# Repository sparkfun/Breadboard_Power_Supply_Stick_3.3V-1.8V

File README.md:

SparkFun Breadboard Power Supply Stick - 3.3V/1.8V
=====================================

[*SparkFun Breadboard Power Supply Stick - 3.3V/1.8V (PRT-10934)*](https://www.sparkfun.com/products/13157)

This is a simple board that takes a 4-9V input voltage and outputs a selectable 1.8V or 3.3V regulated voltage.
All headers are 0.1" pitch for simple insertion into a breadboard. 

Repository Contents
-------------------
* **/Hardware** - All Eagle design files (.brd, .sch, .STL)
* **/Production** - Test bed files and production panel files

Product Versions
----------------
* [PRT-13157](https://www.sparkfun.com/products/13157)- Version 1.4. Currently available
* [PRT-10934](https://www.sparkfun.com/products/10934)- Version 1.0. Retired. 

Version History
---------------
* [v_14](https://github.com/sparkfun/Breadboard_Power_Supply_Stick_3.3V-1.8V/tree/v_14) GitHub files - version 1.4.  
* [v_10](https://github.com/sparkfun/Breadboard_Power_Supply_Stick_3.3V-1.8V/tree/v_10) GitHub files - version 1.0

License Information
-------------------
The hardware is released under [Creative Commons ShareAlike 4.0 International](https://creativecommons.org/licenses/by-sa/4.0/).

Distributed as-is; no warranty is given.

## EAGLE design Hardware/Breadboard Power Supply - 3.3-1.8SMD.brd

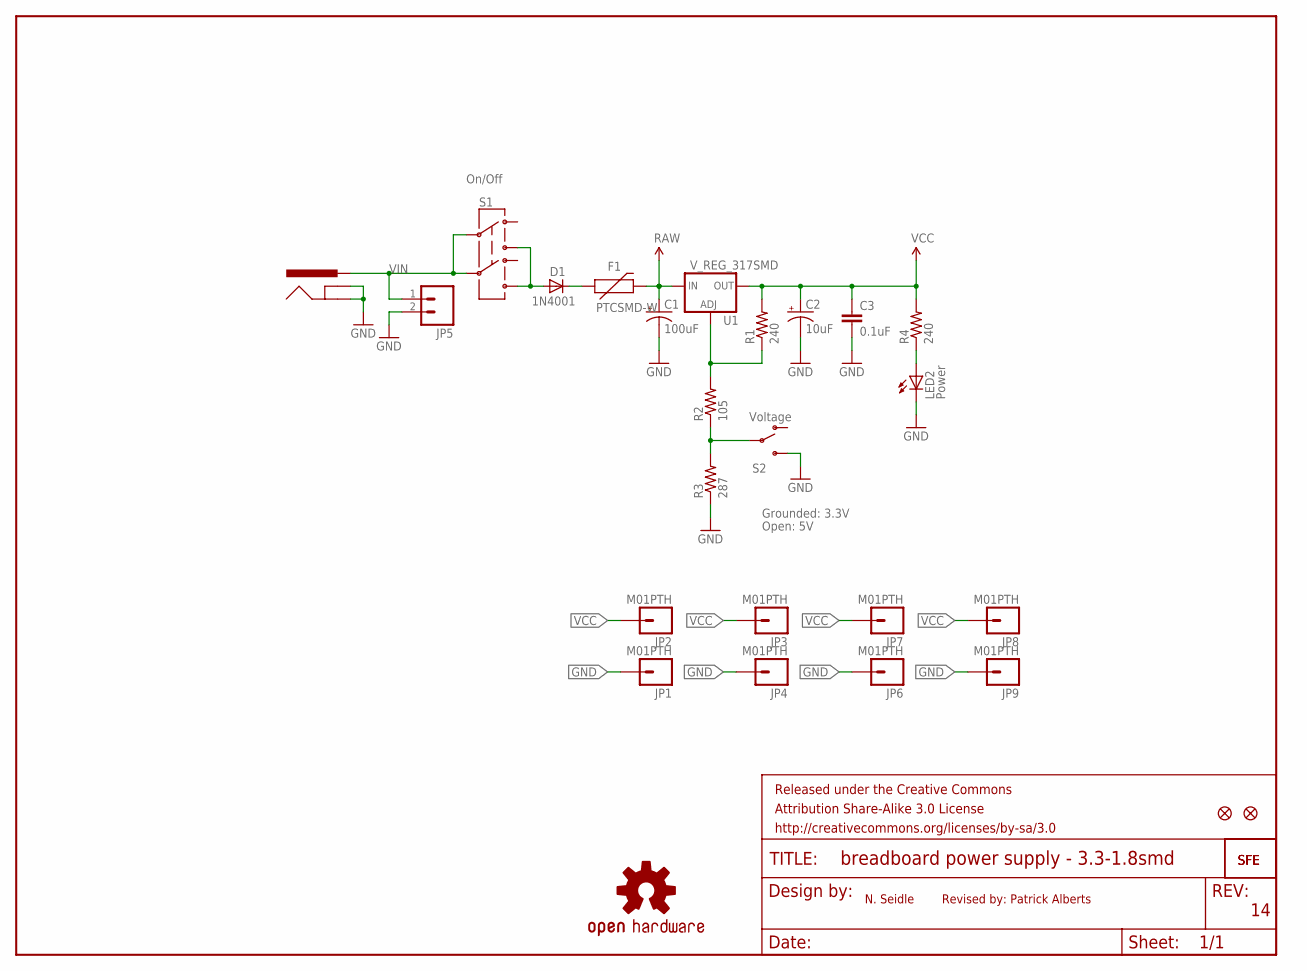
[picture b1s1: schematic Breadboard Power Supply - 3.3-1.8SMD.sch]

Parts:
C1: 100uF; EIA7343
C2: 10uF; EIA3216
C3: 0.1uF; 0603-CAP
D1: 1N4001; SMA-DIODE-TYLERALT1
F1: PTCSMD-W; PTC-1206-WIDE
FRAME1: FRAME-LETTER; CREATIVE_COMMONS
J1: POWER_JACKOVERPASTE_REDBOARD_0603; POWER_JACK_SMD_OVERPASTE_REDBOARD_0603
JP1, JP2, JP3, JP4, JP6, JP7, JP8, JP9: M01PTH; 1X01
JP5: M02PTH; 1X02
LED2: Power; LED-1206
LOGO1: OSHW-LOGOS; OSHW-LOGO-S
R1, R4: 240; 0603-RES
R2: 105; 0603-RES
R3: 287; 0603-RES
S1: On/Off; AYZ0202
S2: Voltage; AYZ0202
U1: V_REG_317SMD; SOT223
U$1: LOGO-SFESK; SFE-LOGO-FLAME
U$2: LOGO-SFENEW; SFE-NEW-WEBLOGO
U$3, U$4: FIDUCIAL1X2; FIDUCIAL-1X2

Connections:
GND: C1.C (-), C2.C (-), C3.2, J1.GND (GNDBREAK), J1.P$4 (GND), JP1.1, JP4.1, JP5.2, JP6.1, JP9.1, LED2.C, R3.1, S2.3 (S)
unnamed: D1.C, F1.1
unnamed: D1.A, S1.1 (3), S1.4 (6)
unnamed: R2.1, R3.2, S2.2
unnamed: R1.1, R2.2, U1.1 (ADJ)
unnamed: LED2.A, R4.1
RAW: C1.A (+), F1.2, U1.3 (IN)
VCC: C2.A (+), C3.1, JP2.1, JP3.1, JP7.1, JP8.1, R1.2, R4.2, U1.2 (OUT)
VIN: J1.VIN0 (PWR), JP5.1, S1.2, S1.5

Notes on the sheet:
Grounded: 3.3V
Open: 5V
N. Seidle
Revised by: Patrick Alberts

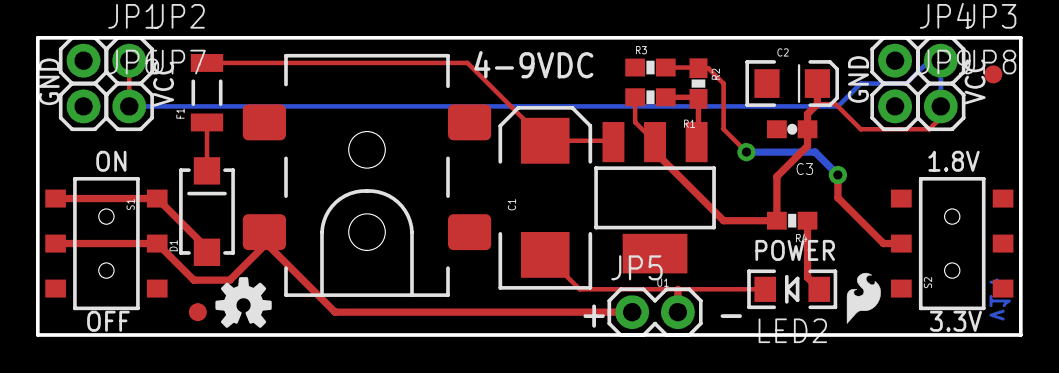
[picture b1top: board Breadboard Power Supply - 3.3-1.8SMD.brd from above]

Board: 2 copper layers, 54.6 x 16.5 mm, 29 parts (1 on the bottom side), 9 nets.

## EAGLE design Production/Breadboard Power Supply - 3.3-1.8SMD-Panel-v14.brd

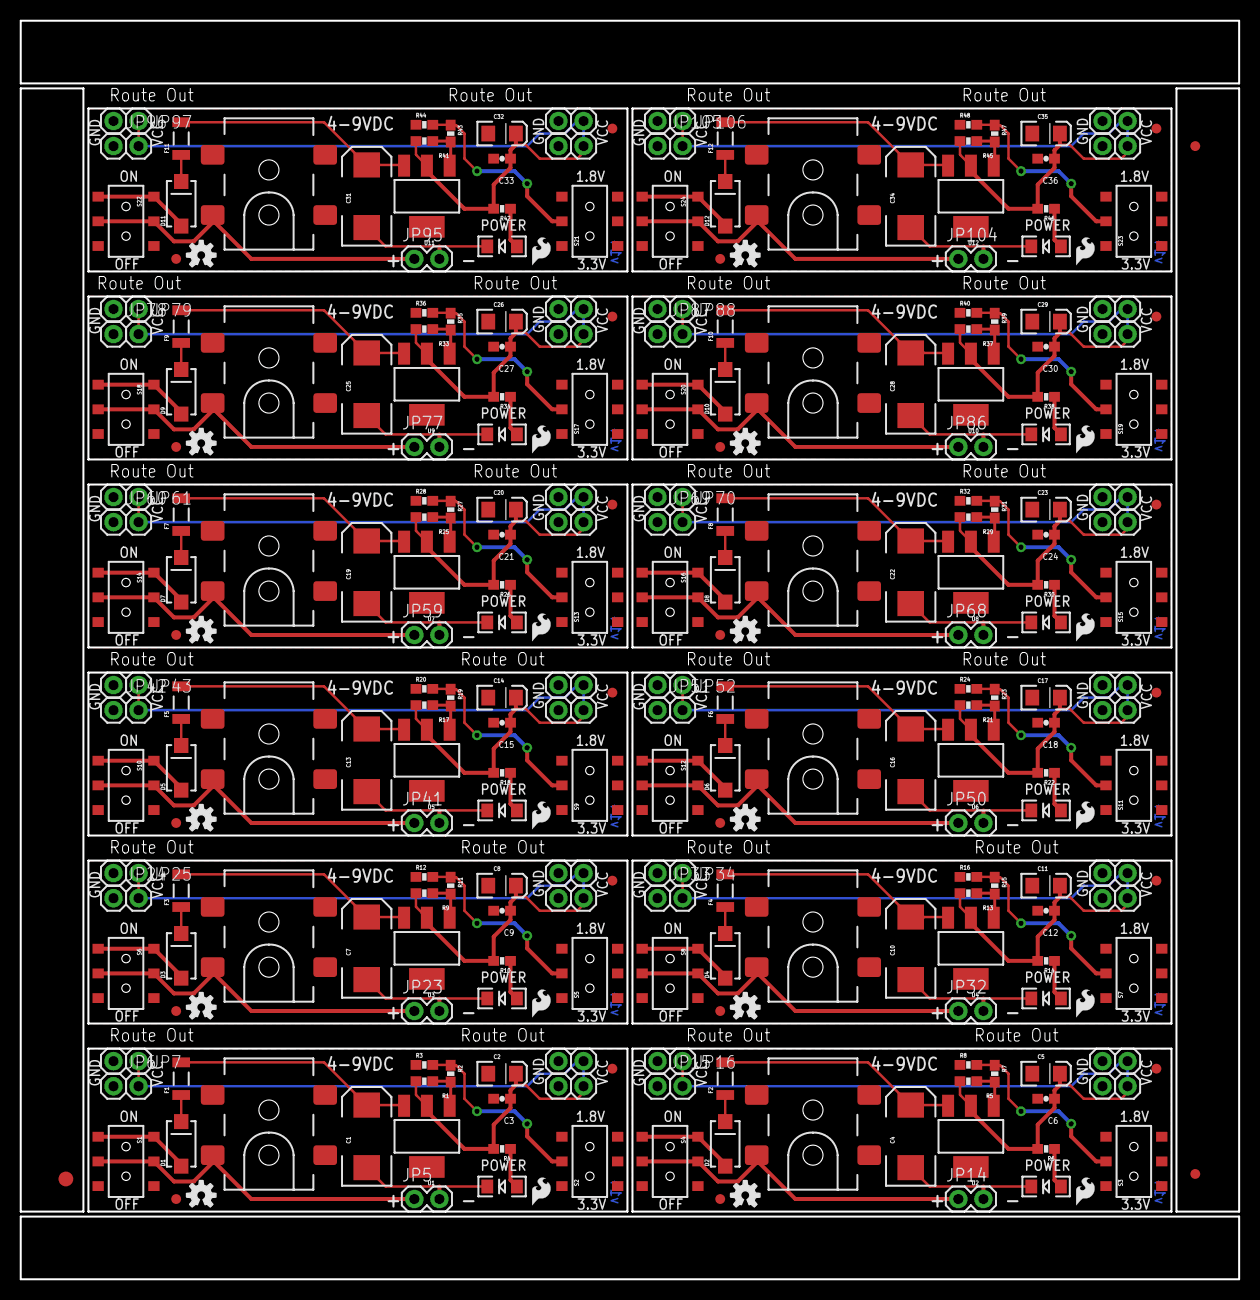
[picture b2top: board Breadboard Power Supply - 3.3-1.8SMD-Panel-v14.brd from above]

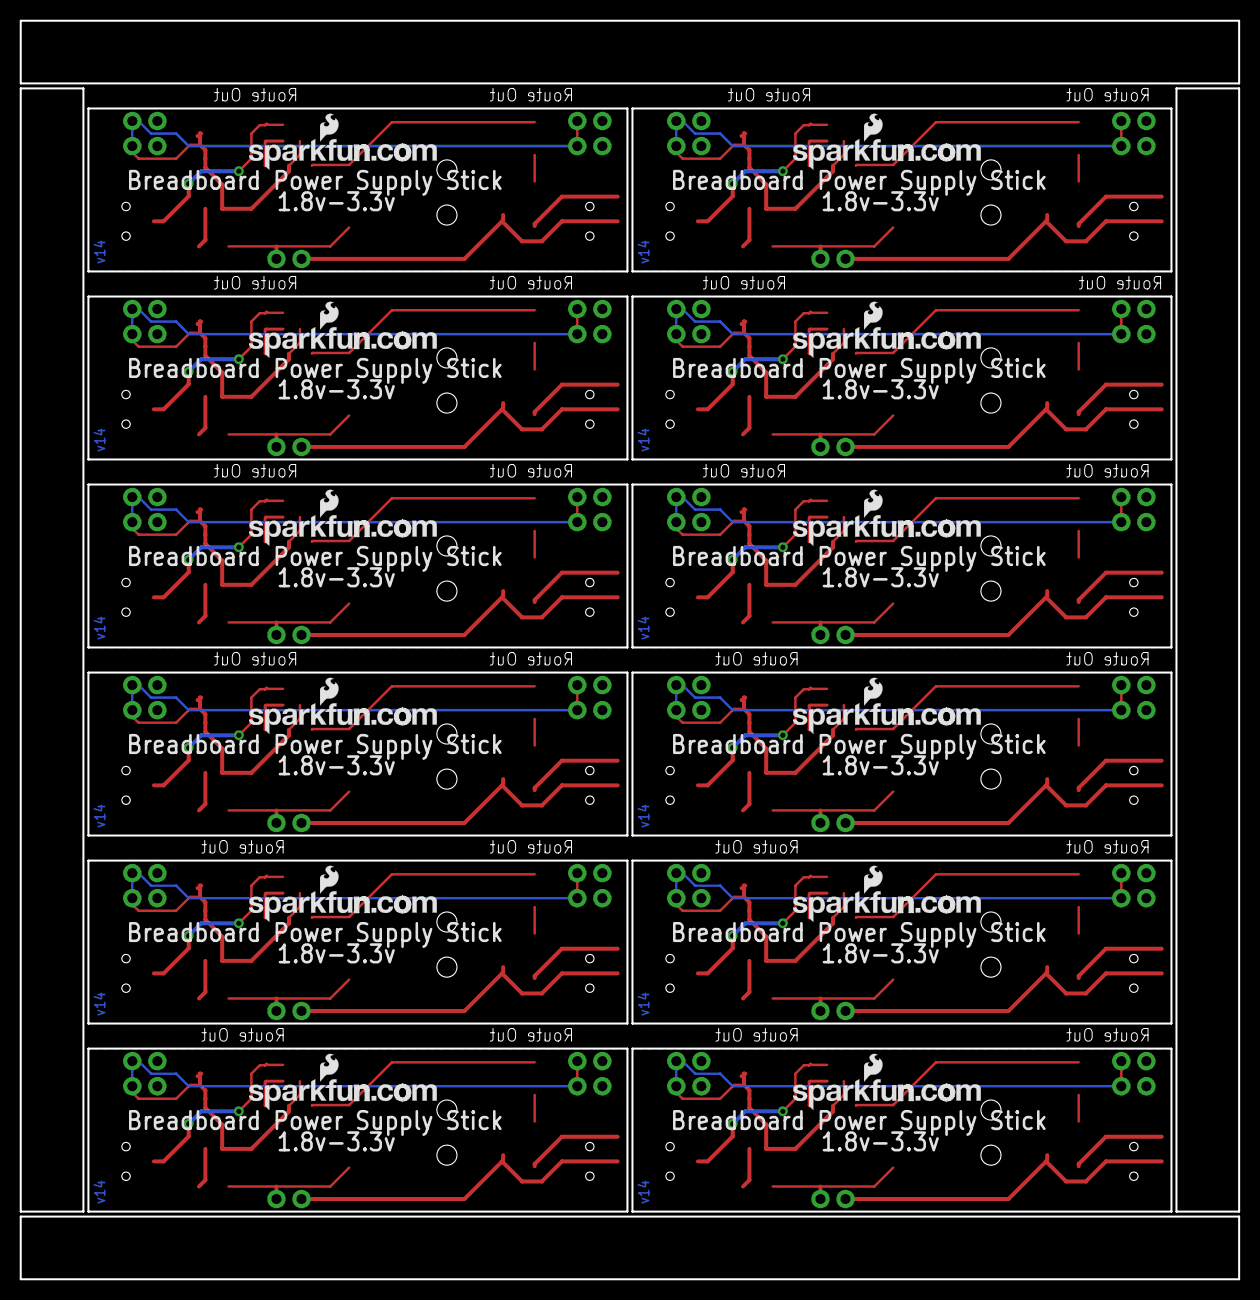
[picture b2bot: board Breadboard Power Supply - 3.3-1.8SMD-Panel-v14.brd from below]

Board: 2 copper layers, 123.4 x 127.5 mm, 339 parts (12 on the bottom side), 108 nets.

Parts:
C1, C4, C7, C10, C13, C16, C19, C22, C25, C28, C31, C34: 100uF; EIA7343
C2, C5, C8, C11, C14, C17, C20, C23, C26, C29, C32, C35: 10uF; EIA3216
C3, C6, C9, C12, C15, C18, C21, C24, C27, C30, C33, C36: 0.1uF; 0603-CAP
D1, D2, D3, D4, D5, D6, D7, D8, D9, D10, D11, D12: 1N4001; SMA-DIODE-TYLERALT1
E$1: FIDUCIAL-1.5X3
E$4, E$6: FIDUCIAL-1X2
F1, F2, F3, F4, F5, F6, F7, F8, F9, F10, F11, F12: PTCSMD-W; PTC-1206-WIDE
J1, J2, J3, J4, J5, J6, J7, J8, J9, J10, J11, J12: POWER_JACKOVERPASTE_REDBOARD_0603; POWER_JACK_SMD_OVERPASTE_REDBOARD_0603
JP1, JP2, JP3, JP4, JP6, JP7, JP8, JP9, JP10, JP11, JP12, JP13, JP15, JP16, JP17, JP18, JP19, JP20, JP21, JP22, JP24, JP25, JP26, JP27, JP28, JP29, JP30, JP31, JP33, JP34, JP35, JP36, JP37, JP38, JP39, JP40, JP42, JP43, JP44, JP45, JP46, JP47, JP48, JP49, JP51, JP52, JP53, JP54, JP55, JP56, JP57, JP58, JP60, JP61, JP62, JP63, JP64, JP65, JP66, JP67, JP69, JP70, JP71, JP72, JP73, JP74, JP75, JP76, JP78, JP79, JP80, JP81, JP82, JP83, JP84, JP85, JP87, JP88, JP89, JP90, JP91, JP92, JP93, JP94, JP96, JP97, JP98, JP99, JP100, JP101, JP102, JP103, JP105, JP106, JP107, JP108: M01PTH; 1X01
JP5, JP14, JP23, JP32, JP41, JP50, JP59, JP68, JP77, JP86, JP95, JP104: 1X02
LED1, LED2, LED3, LED4, LED5, LED6, LED7, LED8, LED9, LED10, LED11, LED12: Power; LED-1206
LOGO1, LOGO2, LOGO3, LOGO4, LOGO5, LOGO6, LOGO7, LOGO8, LOGO9, LOGO10, LOGO11, LOGO12: OSHW-LOGOS; OSHW-LOGO-S
R1, R4, R5, R6, R9, R10, R13, R14, R17, R18, R21, R22, R25, R26, R29, R30, R33, R34, R37, R38, R41, R42, R45, R46: 240; 0603-RES
R2, R7, R11, R15, R19, R23, R27, R31, R35, R39, R43, R47: 105; 0603-RES
R3, R8, R12, R16, R20, R24, R28, R32, R36, R40, R44, R48: 287; 0603-RES
S1, S4, S6, S8, S10, S12, S14, S16, S18, S20, S22, S24: On/Off; AYZ0202
S2, S3, S5, S7, S9, S11, S13, S15, S17, S19, S21, S23: Voltage; AYZ0202
U1, U2, U3, U4, U5, U6, U7, U8, U9, U10, U11, U12: V_REG_317SMD; SOT223
U$1, U$5, U$9, U$13, U$17, U$21, U$25, U$29, U$33, U$37, U$41, U$45: LOGO-SFESK; SFE-LOGO-FLAME
U$2, U$6, U$10, U$14, U$18, U$22, U$26, U$30, U$34, U$38, U$42, U$46: LOGO-SFENEW; SFE-NEW-WEBLOGO
U$3, U$4, U$7, U$8, U$11, U$12, U$15, U$16, U$19, U$20, U$23, U$24, U$27, U$28, U$31, U$32, U$35, U$36, U$39, U$40, U$43, U$44, U$47, U$48: FIDUCIAL1X2; FIDUCIAL-1X2

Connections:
GND: C1.C, C2.C, C3.2, J1.GND, J1.P$4, JP1.1, JP4.1, JP5.2, JP6.1, JP9.1, LED2.C, R3.1, S2.3
GND1: C4.C, C5.C, C6.2, J2.GND, J2.P$4, JP10.1, JP13.1, JP14.2, JP15.1, JP18.1, LED1.C, R8.1, S3.3
GND2: C7.C, C8.C, C9.2, J3.GND, J3.P$4, JP19.1, JP22.1, JP23.2, JP24.1, JP27.1, LED3.C, R12.1, S5.3
GND3: C10.C, C11.C, C12.2, J4.GND, J4.P$4, JP28.1, JP31.1, JP32.2, JP33.1, JP36.1, LED4.C, R16.1, S7.3
GND4: C13.C, C14.C, C15.2, J5.GND, J5.P$4, JP37.1, JP40.1, JP41.2, JP42.1, JP45.1, LED5.C, R20.1, S9.3
GND5: C16.C, C17.C, C18.2, J6.GND, J6.P$4, JP46.1, JP49.1, JP50.2, JP51.1, JP54.1, LED6.C, R24.1, S11.3
GND6: C19.C, C20.C, C21.2, J7.GND, J7.P$4, JP55.1, JP58.1, JP59.2, JP60.1, JP63.1, LED7.C, R28.1, S13.3
GND7: C22.C, C23.C, C24.2, J8.GND, J8.P$4, JP64.1, JP67.1, JP68.2, JP69.1, JP72.1, LED8.C, R32.1, S15.3
GND8: C25.C, C26.C, C27.2, J9.GND, J9.P$4, JP73.1, JP76.1, JP77.2, JP78.1, JP81.1, LED9.C, R36.1, S17.3
GND9: C28.C, C29.C, C30.2, J10.GND, J10.P$4, JP82.1, JP85.1, JP86.2, JP87.1, JP90.1, LED10.C, R40.1, S19.3
GND10: C31.C, C32.C, C33.2, J11.GND, J11.P$4, JP91.1, JP94.1, JP95.2, JP96.1, JP99.1, LED11.C, R44.1, S21.3
GND11: C34.C, C35.C, C36.2, J12.GND, J12.P$4, JP100.1, JP103.1, JP104.2, JP105.1, JP108.1, LED12.C, R48.1, S23.3
unnamed: D1.C, F1.1
unnamed: D1.A, S1.1, S1.4
unnamed: R5.1, R7.2, U2.1
unnamed: R2.1, R3.2, S2.2
unnamed: R1.1, R2.2, U1.1
unnamed: LED1.A, R6.1
unnamed: D2.C, F2.1
unnamed: LED2.A, R4.1
unnamed: D2.A, S4.1, S4.4
unnamed: R7.1, R8.2, S3.2
unnamed: R9.1, R11.2, U3.1
unnamed: LED3.A, R10.1
unnamed: D3.C, F3.1
unnamed: D3.A, S6.1, S6.4
unnamed: R11.1, R12.2, S5.2
unnamed: R13.1, R15.2, U4.1
unnamed: LED4.A, R14.1
unnamed: D4.C, F4.1
unnamed: D4.A, S8.1, S8.4
unnamed: R15.1, R16.2, S7.2
unnamed: R17.1, R19.2, U5.1
unnamed: LED5.A, R18.1
unnamed: D5.C, F5.1
unnamed: D5.A, S10.1, S10.4
unnamed: R19.1, R20.2, S9.2
unnamed: R21.1, R23.2, U6.1
unnamed: LED6.A, R22.1
unnamed: D6.C, F6.1
unnamed: D6.A, S12.1, S12.4
unnamed: R23.1, R24.2, S11.2
unnamed: R25.1, R27.2, U7.1
unnamed: LED7.A, R26.1
unnamed: D7.C, F7.1
unnamed: D7.A, S14.1, S14.4
unnamed: R27.1, R28.2, S13.2
unnamed: R29.1, R31.2, U8.1
unnamed: LED8.A, R30.1
unnamed: D8.C, F8.1
unnamed: D8.A, S16.1, S16.4
unnamed: R31.1, R32.2, S15.2
unnamed: R33.1, R35.2, U9.1
unnamed: LED9.A, R34.1
unnamed: D9.C, F9.1
unnamed: D9.A, S18.1, S18.4
unnamed: R35.1, R36.2, S17.2
unnamed: R37.1, R39.2, U10.1
unnamed: LED10.A, R38.1
unnamed: D10.C, F10.1
unnamed: D10.A, S20.1, S20.4
unnamed: R39.1, R40.2, S19.2
unnamed: R41.1, R43.2, U11.1
unnamed: LED11.A, R42.1
unnamed: D11.C, F11.1
unnamed: D11.A, S22.1, S22.4
unnamed: R43.1, R44.2, S21.2
unnamed: R45.1, R47.2, U12.1
unnamed: LED12.A, R46.1
unnamed: D12.C, F12.1
unnamed: D12.A, S24.1, S24.4
unnamed: R47.1, R48.2, S23.2
RAW: C1.A, F1.2, U1.3
RAW1: C4.A, F2.2, U2.3
RAW2: C7.A, F3.2, U3.3
RAW3: C10.A, F4.2, U4.3
RAW4: C13.A, F5.2, U5.3
RAW5: C16.A, F6.2, U6.3
RAW6: C19.A, F7.2, U7.3
RAW7: C22.A, F8.2, U8.3
RAW8: C25.A, F9.2, U9.3
RAW9: C28.A, F10.2, U10.3
RAW10: C31.A, F11.2, U11.3
RAW11: C34.A, F12.2, U12.3
VCC: C2.A, C3.1, JP2.1, JP3.1, JP7.1, JP8.1, R1.2, R4.2, U1.2
VCC1: C5.A, C6.1, JP11.1, JP12.1, JP16.1, JP17.1, R5.2, R6.2, U2.2
VCC2: C8.A, C9.1, JP20.1, JP21.1, JP25.1, JP26.1, R9.2, R10.2, U3.2
VCC3: C11.A, C12.1, JP29.1, JP30.1, JP34.1, JP35.1, R13.2, R14.2, U4.2
VCC4: C14.A, C15.1, JP38.1, JP39.1, JP43.1, JP44.1, R17.2, R18.2, U5.2
VCC5: C17.A, C18.1, JP47.1, JP48.1, JP52.1, JP53.1, R21.2, R22.2, U6.2
VCC6: C20.A, C21.1, JP56.1, JP57.1, JP61.1, JP62.1, R25.2, R26.2, U7.2
VCC7: C23.A, C24.1, JP65.1, JP66.1, JP70.1, JP71.1, R29.2, R30.2, U8.2
VCC8: C26.A, C27.1, JP74.1, JP75.1, JP79.1, JP80.1, R33.2, R34.2, U9.2
VCC9: C29.A, C30.1, JP83.1, JP84.1, JP88.1, JP89.1, R37.2, R38.2, U10.2
VCC10: C32.A, C33.1, JP92.1, JP93.1, JP97.1, JP98.1, R41.2, R42.2, U11.2
VCC11: C35.A, C36.1, JP101.1, JP102.1, JP106.1, JP107.1, R45.2, R46.2, U12.2
VIN: J1.VIN0, JP5.1, S1.2, S1.5
VIN1: J2.VIN0, JP14.1, S4.2, S4.5
VIN2: J3.VIN0, JP23.1, S6.2, S6.5
VIN3: J4.VIN0, JP32.1, S8.2, S8.5
VIN4: J5.VIN0, JP41.1, S10.2, S10.5
VIN5: J6.VIN0, JP50.1, S12.2, S12.5
VIN6: J7.VIN0, JP59.1, S14.2, S14.5
VIN7: J8.VIN0, JP68.1, S16.2, S16.5
VIN8: J9.VIN0, JP77.1, S18.2, S18.5
VIN9: J10.VIN0, JP86.1, S20.2, S20.5
VIN10: J11.VIN0, JP95.1, S22.2, S22.5
VIN11: J12.VIN0, JP104.1, S24.2, S24.5

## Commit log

2013-12-09 Uploaded SCH/BRD files
2013-12-09 Revert "Uploaded SCH/BRD files"
    This reverts commit d8db60096a53af6743d0e5566ef11829b60b235d.
2014-05-14 Added board name, 0603 footprint, barrel jack...
    as well as updated the diode.
2014-06-19 changed barrel jack footprint
2014-06-20 Changed RES position, fixed airwires
2014-06-20 created panel v14
2014-08-07 Updating to current board files
2014-08-07 Adding back in rev files
2015-02-04 Corrected eagle files. Removed version # from name.
    These files don't pass our current QC checklist but they are current to
    the storefront product.

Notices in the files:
parts and their libraries:
SparkFun-Aesthetics: Licensing: CC v3.0 Share-Alike You are welcome to use this library for commercial purposes.
SparkFun-Aesthetics: Released under the Creative Commons Attribution Share-Alike 3.0 License
SparkFun-Aesthetics: http://creativecommons.org/licenses/by-sa/3.0
